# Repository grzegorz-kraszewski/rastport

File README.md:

# rastport
Opensourced hardware projects from RastPort

All projects in this repository are licensed on Creative Commons [Attribution 4.0 International](http://creativecommons.org/licenses/by/4.0/?ref=chooser-v1).

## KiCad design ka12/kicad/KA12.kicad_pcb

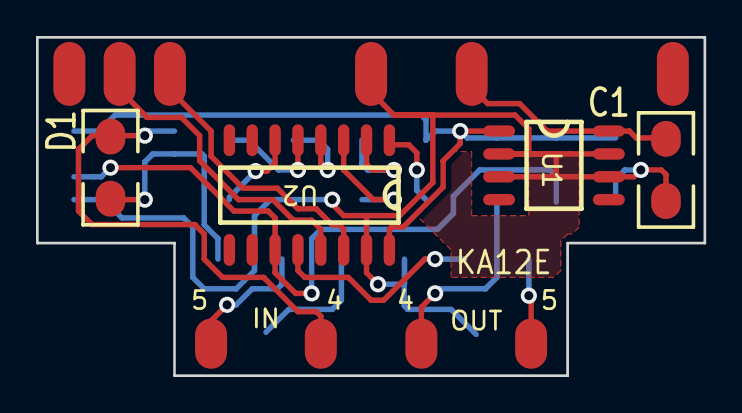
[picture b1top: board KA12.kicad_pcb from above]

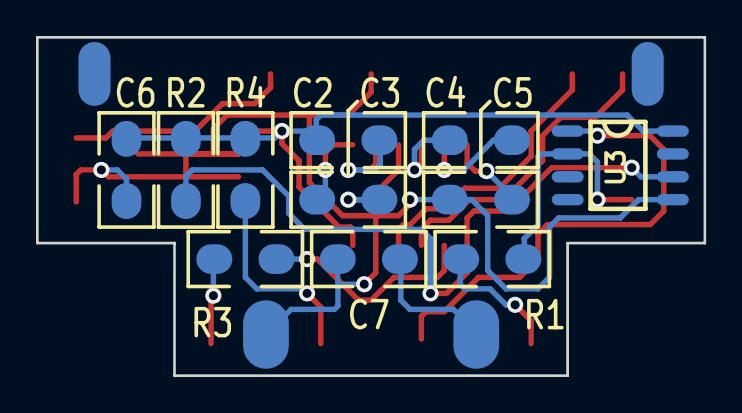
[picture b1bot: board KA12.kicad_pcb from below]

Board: 2 copper layers, 37.1 x 18.8 mm, 22 parts (11 on the bottom side), 19 nets.

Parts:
C1, C2, C3, C4, C5, C6: 100n; 1206M
C7: 100p; 1206M
CN1: AMIGA RS-232; DB25_EDGE
D1: 1N4148; 1206M
J1: IN; PAD12
J2, J5: 4; PAD08
J3, J6: 5; PAD08
J4: OUT; PAD12
R1, R3, R4: 220R; 1206M
R2: 3k3; 1206M
U1: 78L05; SO8M
U2: MAX232A; SO16M
U3: IL207; SO8M

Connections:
unnamed: C3.1, U2.3
unnamed: C5.2, U2.6
unnamed: CN1.2, U2.13
unnamed: J3.1, R1.1
unnamed: CN1.3, U2.14
unnamed: R3.1, U2.12
unnamed: C3.2, U2.1
unnamed: C4.2, U2.4
unnamed: C4.1, U2.5
unnamed: C2.1, U2.2
unnamed: C7.1, J1.1
unnamed: D1.2, J2.1, U3.1
unnamed: D1.1, R1.2, U3.2
unnamed: R2.2, U2.11, U3.6
unnamed: J6.1, R3.2
unnamed: J5.1, R4.2
unnamed: C1.1, CN1.9, U1.8
unnamed: C2.2, C6.2, R2.1, R4.1, U1.1, U2.16, U3.8
unnamed: C1.2, C5.1, C6.1, C7.2, CN1.7, J4.1, U1.2, U1.3, U1.6, U1.7, U2.15, U3.5

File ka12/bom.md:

|Reference|Description|Quantity|
|---------|-----------|--------|
|–|PCB|1|
|U1|Dual RS232 transmitter/receiver; MAX232A, ST232C or equivalent; SO16|1|
|U2|+5 V fixed voltage regulator; ST78L05 or equivalent; SO8|1|
|U3|Optocoupler; IL207 or MOC207; SO8|1|
|D1|Switching diode; 1N4148; 1206|1|
|C1-C6|MLCC capacitor; 100 nF, 50 V, X7R, ±10%; 1206|6|
|C7|MLCC capacitor; 100 pF, 50 V, C0G, ±10%; 1206|1|
|R1, R3, R4|Thick film resistor; 220 Ω, 0.25 W, ±5%; 1206|3|
|R2|Thick film resistor; 3.3 kΩ, 0.25 W, ±5%; 1206|1|
|CN1|D-Sub 25 pin female plug, for cable|1|
|CN1|D-Sub 25 pin shell|1|
|–|Data transmission cable, LiYCY 2 × 0.25 mm², braided shield|3 m|
|–|DIN 5 plug, Rean NYS232|2|
|–|Heat shrink tube 1.6 mm, black|16 mm|
|–|Heat shrink tube 4.8 mm, black|90 mm|
|–|Heat shrink tube 4.8 mm, red|90 mm|
|–|Plastic transparent fuel pipe 7/10 mm|30 mm|

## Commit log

2023-03-27 Update README.md
    Added licensing statement.
2023-03-27 KA12 MIDI interface initial import.
2023-03-28 Fixed DIN5 plug symbol.
2023-10-19 Added new project: KA71 headphone amplifier with channel cross-mixing. Added empty BOM.
2023-10-19 Entered all components to BOM
2023-11-29 Update bom.md
    Changed value of R2 from 3.3 kΩ to 2.2 kΩ. Important when using MOC207 optocoupler instead of IL207. MOC is slower, so with 3.3 kΩ resistor slew rate is too low for 31250 bps.
